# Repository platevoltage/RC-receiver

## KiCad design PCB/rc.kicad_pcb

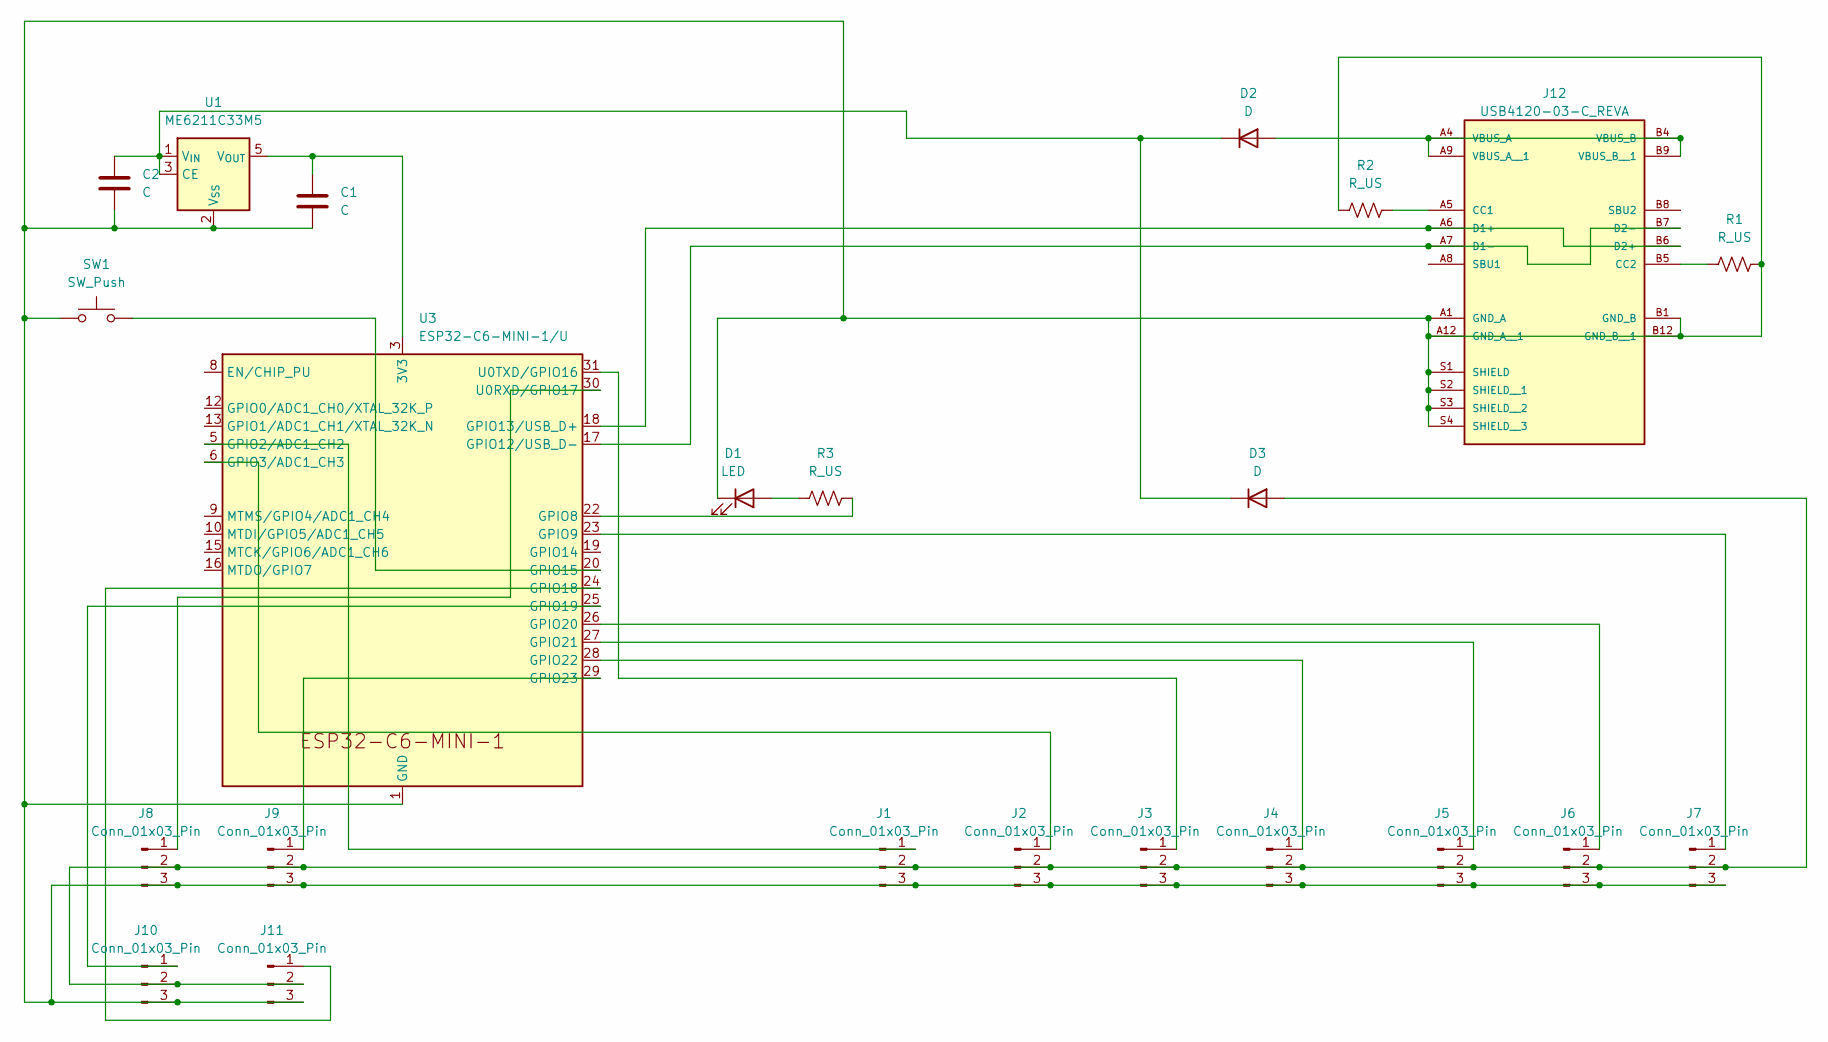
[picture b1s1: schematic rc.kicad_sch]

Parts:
C1, C2: C; C_0402_1005Metric_Pad0.74x0.62mm_HandSolder
D1: LED; LED_D3.0mm
D2, D3: D; D_0603_1608Metric_Pad1.05x0.95mm_HandSolder
J1, J2, J3, J4, J5, J6, J7, J8, J9, J10, J11: Conn_01x03_Pin; PinHeader_1x03_P2.54mm_Vertical
J12: USB4120-03-C_REVA; USB4120-03-C_GCT; PARTREV A
R1, R2, R3: R_US; R_0402_1005Metric_Pad0.72x0.64mm_HandSolder
SW1: SW_Push; SW_Tactile_SPST_NO_Straight_CK_PTS636Sx25SMTRLFS
U1: ME6211C33M5; SOT-23-5
U3: ESP32-C6-MINI-1/U; ESP32-C3-MINI-1_HandSoldering

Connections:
unnamed: D1.2 (A), R3.1
unnamed: C1.2, C2.2, D1.1 (K), J1.3, J2.3, J3.3, J4.3, J5.3, J6.3, J7.3, J8.3, J9.3, J10.3, J11.3, J12.A1 (GND_A), J12.A12 (GND_A__1), J12.B1 (GND_B), J12.B12 (GND_B__1), J12.S1 (SHIELD), J12.S2 (SHIELD__1), J12.S3 (SHIELD__2), J12.S4 (SHIELD__3), R1.1, R2.1, SW1.1, U1.2 (V_{SS}), U3.1 (GND), U3.2 (GND), U3.11 (GND), U3.14 (GND), U3.36 (GND), U3.37 (GND), U3.38 (GND), U3.39 (GND), U3.40 (GND), U3.41 (GND), U3.42 (GND), U3.43 (GND), U3.44 (GND), U3.45 (GND), U3.46 (GND), U3.47 (GND), U3.48 (GND), U3.49 (GND), U3.50 (GND), U3.51 (GND), U3.52 (GND), U3.53 (GND)
unnamed: D2.2 (A), J12.A4 (VBUS_A), J12.A9 (VBUS_A__1), J12.B4 (VBUS_B), J12.B9 (VBUS_B__1)
unnamed: C2.1, D2.1 (K), D3.1 (K), U1.1 (V_{IN}), U1.3 (CE)
unnamed: D3.2 (A), J1.2, J2.2, J3.2, J4.2, J5.2, J6.2, J7.2, J8.2, J9.2, J10.2, J11.2
unnamed: J1.1, U3.5 (GPIO2/ADC1_CH2)
unnamed: J2.1, U3.6 (GPIO3/ADC1_CH3)
unnamed: J3.1, U3.31 (U0TXD/GPIO16)
unnamed: J4.1, U3.28 (GPIO22)
unnamed: J5.1, U3.27 (GPIO21)
unnamed: J6.1, U3.26 (GPIO20)
unnamed: J7.1, U3.23 (GPIO9)
unnamed: J8.1, U3.30 (U0RXD/GPIO17)
unnamed: J9.1, U3.29 (GPIO23)
unnamed: J10.1, U3.25 (GPIO19)
unnamed: J11.1, U3.24 (GPIO18)
unnamed: J12.A5 (CC1), R2.2
unnamed: J12.B5 (CC2), R1.2
unnamed: J12.A6 (D1+), J12.B6 (D2+), U3.18 (GPIO13/USB_D+)
unnamed: J12.A7 (D1-), J12.B7 (D2-), U3.17 (GPIO12/USB_D-)
unnamed: C1.1, U1.5 (V_{OUT}), U3.3 (3V3)
unnamed: R3.2, U3.22 (GPIO8)
unnamed: SW1.2, U3.20 (GPIO15)

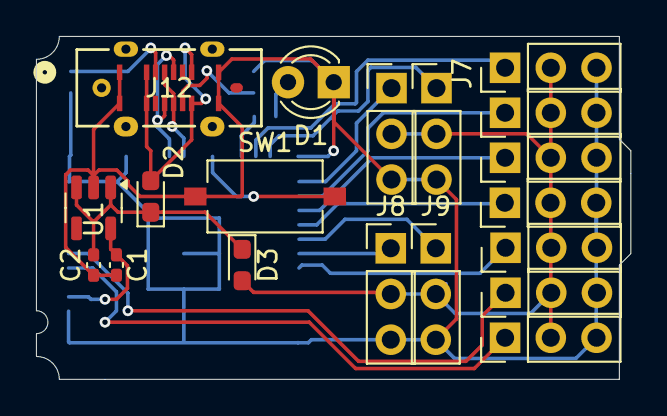
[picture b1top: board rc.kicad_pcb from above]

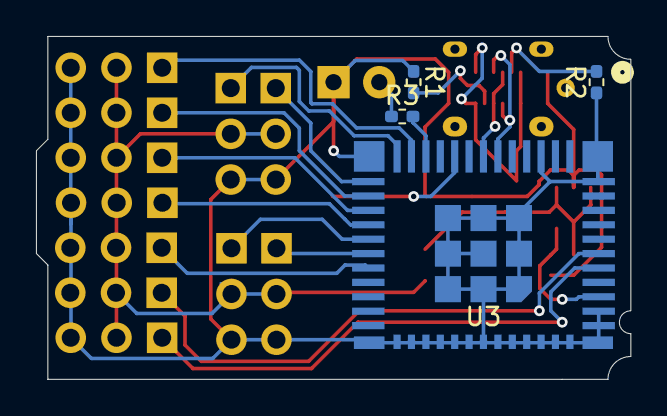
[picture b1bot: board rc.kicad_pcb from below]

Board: 2 copper layers, 33.0 x 19.0 mm, 23 parts (4 on the bottom side), 23 nets.

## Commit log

2024-07-04 init
2024-07-12 smaller
2024-07-13 more components
2024-07-14 diodes
